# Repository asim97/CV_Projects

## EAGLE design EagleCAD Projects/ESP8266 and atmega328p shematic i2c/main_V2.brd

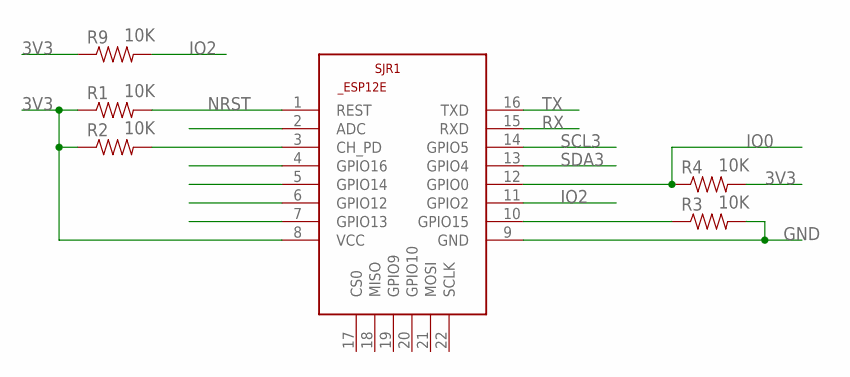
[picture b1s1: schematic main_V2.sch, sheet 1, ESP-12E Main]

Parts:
R1, R2, R3, R4, R9: 10K; 1206
SJR1: ESP8266-12EESP12E; ESP8266-ESP12E

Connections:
3V3: R1.1, R2.1, R4.2, R9.1, SJR1.8 (VCC); also elsewhere on the board
GND: R3.2, SJR1.9 (GND); also elsewhere on the board
IO0: R4.1, SJR1.12 (GPIO0); also elsewhere on the board
IO2: R9.2, SJR1.11 (GPIO2)
unnamed: R2.2, SJR1.3 (CH_PD)
unnamed: R3.1, SJR1.10 (GPIO15)
NRST: R1.2, SJR1.1 (REST); also elsewhere on the board
RX: SJR1.15 (RXD); also elsewhere on the board
SCL3: SJR1.14 (GPIO5); also elsewhere on the board
SDA3: SJR1.13 (GPIO4); also elsewhere on the board
TX: SJR1.16 (TXD); also elsewhere on the board

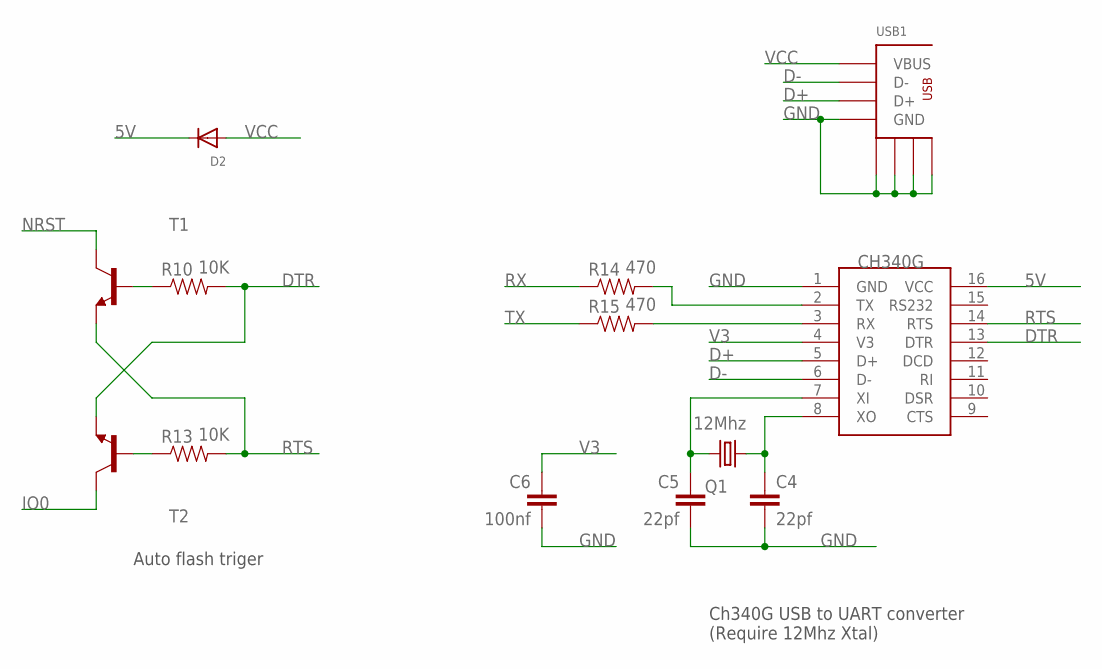
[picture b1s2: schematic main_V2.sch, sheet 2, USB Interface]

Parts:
C4, C5: 22pf; C1206K
C6: 100nf; C1206K
D2: DIODESMA; SMADIODE
Q1: 12Mhz; CSM-7X-DU
R10, R13: 10K; 1206
R14, R15: 470; 1206
T1, T2: MMBT5551LT1-NPN-SOT23-BEC; SOT23-BEC
U$1: CH340G; SOIC16
USB1: USB3MINI; USB-MB-S

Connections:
5V: D2.C, U$1.16 (VCC); also elsewhere on the board
D+: U$1.5 (D+), USB1.D+
D-: U$1.6 (D-), USB1.D-
DTR: R10.2, T2.E, U$1.13 (DTR)
GND: C4.2, C5.2, C6.2, U$1.1 (GND), USB1.GND, USB1.P$1 (GND), USB1.P$2 (GND), USB1.P$3 (GND), USB1.P$4 (GND); also elsewhere on the board
IO0: T2.C; also elsewhere on the board
unnamed: C4.1, Q1.1, U$1.8 (XO)
unnamed: C5.1, Q1.2, U$1.7 (XI)
unnamed: R10.1, T1.B
unnamed: R13.1, T2.B
unnamed: R15.2, U$1.3 (RX)
unnamed: R14.2, U$1.2 (TX)
NRST: T1.C; also elsewhere on the board
RTS: R13.2, T1.E, U$1.14 (RTS)
RX: R14.1; also elsewhere on the board
TX: R15.1; also elsewhere on the board
V3: C6.1, U$1.4 (V3)
VCC: D2.A, USB1.VBUS

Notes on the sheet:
Auto flash triger
Ch340G USB to UART converter (Require 12Mhz Xtal)

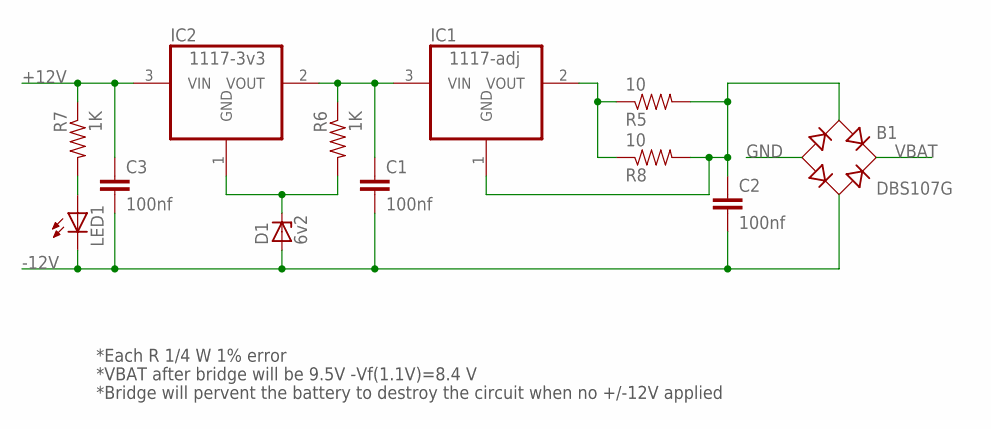
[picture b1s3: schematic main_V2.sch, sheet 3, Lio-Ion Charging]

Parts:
B1: DBS107G; DBS
C1, C2, C3: 100nf; C1206K
D1: 6v2; SOT23
IC1: 1117-adj; SOT223
IC2: 1117-3v3; SOT223
LED1: LEDSMT1206; 1206
R5, R8: 10; 1206
R6, R7: 1K; 1206

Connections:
+12V: C3.1, IC2.3 (VIN), R7.1
-12V: B1.AC2, C1.2, C2.2, C3.2, D1.1 (A), LED1.C
GND: B1.-; also elsewhere on the board
unnamed: D1.3 (C), IC2.1 (GND), R6.2
unnamed: B1.AC1, C2.1, IC1.1 (GND), R5.2, R8.2
unnamed: IC1.2 (VOUT), R5.1, R8.1
unnamed: C1.1, IC1.3 (VIN), IC2.2 (VOUT), R6.1
unnamed: LED1.A, R7.2
VBAT: B1.+; also elsewhere on the board

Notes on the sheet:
*Each R 1/4 W 1% error
*VBAT after bridge will be 9.5V -Vf(1.1V)=8.4 V
*Bridge will pervent the battery to destroy the circuit when no +/-12V applied

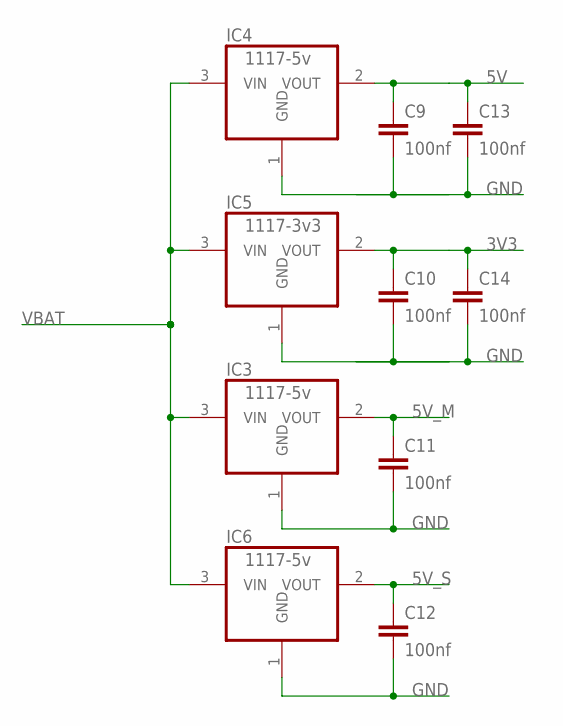
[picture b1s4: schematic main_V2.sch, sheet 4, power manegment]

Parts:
C9, C10, C11, C12, C13, C14: 100nf; C1206K
IC3, IC4, IC6: 1117-5v; SOT223
IC5: 1117-3v3; SOT223

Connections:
3V3: C10.1, C14.1, IC5.2 (VOUT); also elsewhere on the board
5V: C9.1, C13.1, IC4.2 (VOUT); also elsewhere on the board
5V_M: C11.1, IC3.2 (VOUT); also elsewhere on the board
5V_S: C12.1, IC6.2 (VOUT)
GND: C9.2, C10.2, C11.2, C12.2, C13.2, C14.2, IC3.1 (GND), IC4.1 (GND), IC5.1 (GND), IC6.1 (GND); also elsewhere on the board
VBAT: IC3.3 (VIN), IC4.3 (VIN), IC5.3 (VIN), IC6.3 (VIN); also elsewhere on the board

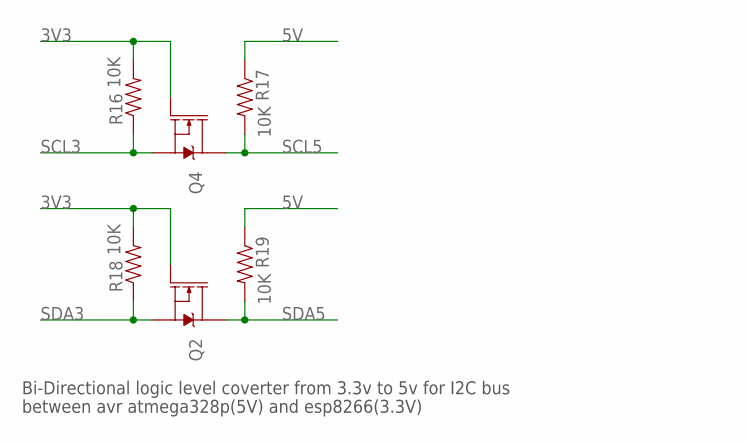
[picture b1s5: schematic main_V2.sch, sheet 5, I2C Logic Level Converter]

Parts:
Q2, Q4: MOSFET-NCH-BSS138; SOT23-3
R16, R17, R18, R19: 10K; 1206

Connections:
3V3: Q2.1 (G), Q4.1 (G), R16.2, R18.2; also elsewhere on the board
5V: R17.1, R19.1; also elsewhere on the board
SCL3: Q4.2 (S), R16.1; also elsewhere on the board
SCL5: Q4.3 (D), R17.2; also elsewhere on the board
SDA3: Q2.2 (S), R18.1; also elsewhere on the board
SDA5: Q2.3 (D), R19.2; also elsewhere on the board

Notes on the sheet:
Bi-Directional logic level coverter from 3.3v to 5v for I2C bus
between avr atmega328p(5V) and esp8266(3.3V)

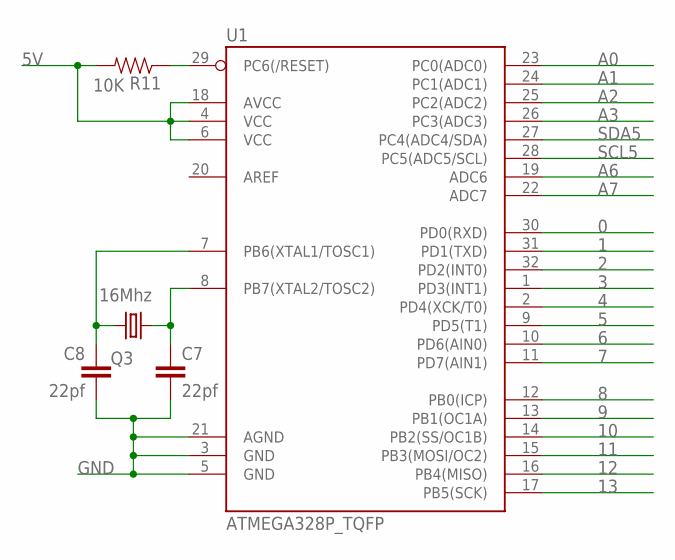
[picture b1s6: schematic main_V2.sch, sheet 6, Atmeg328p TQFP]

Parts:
C7, C8: 22pf; C1206K
Q3: 16Mhz; CSM-7X-DU
R11: 10K; 1206
U1: ATMEGA328P_TQFP; TQFP32-08

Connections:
0: U1.30 (PD0(RXD))
1: U1.31 (PD1(TXD))
2: U1.32 (PD2(INT0))
3: U1.1 (PD3(INT1))
4: U1.2 (PD4(XCK/T0))
5: U1.9 (PD5(T1))
5V: R11.2, U1.4 (VCC), U1.6 (VCC), U1.18 (AVCC); also elsewhere on the board
6: U1.10 (PD6(AIN0))
7: U1.11 (PD7(AIN1))
8: U1.12 (PB0(ICP))
9: U1.13 (PB1(OC1A))
10: U1.14 (PB2(SS/OC1B))
11: U1.15 (PB3(MOSI/OC2))
12: U1.16 (PB4(MISO))
13: U1.17 (PB5(SCK))
A0: U1.23 (PC0(ADC0))
A1: U1.24 (PC1(ADC1))
A2: U1.25 (PC2(ADC2))
A3: U1.26 (PC3(ADC3))
A6: U1.19 (ADC6)
A7: U1.22 (ADC7)
GND: C7.2, C8.2, U1.3 (GND), U1.5 (GND), U1.21 (AGND); also elsewhere on the board
unnamed: C7.1, Q3.1, U1.8 (PB7(XTAL2/TOSC2))
unnamed: C8.1, Q3.2, U1.7 (PB6(XTAL1/TOSC1))
unnamed: R11.1, U1.29 (PC6(/RESET))
SCL5: U1.28 (PC5(ADC5/SCL)); also elsewhere on the board
SDA5: U1.27 (PC4(ADC4/SDA)); also elsewhere on the board

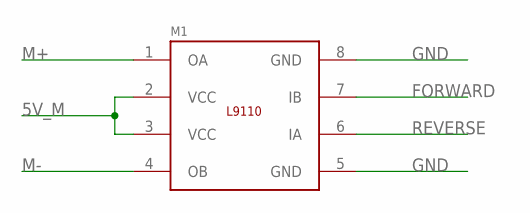
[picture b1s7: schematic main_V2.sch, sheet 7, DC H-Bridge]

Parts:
M1: L9110; SO8P

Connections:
5V_M: M1.2 (VCC), M1.3 (VCC); also elsewhere on the board
FORWARD: M1.7 (IB)
GND: M1.5 (GND), M1.8 (GND); also elsewhere on the board
M+: M1.1 (OA)
M-: M1.4 (OB)
REVERSE: M1.6 (IA)

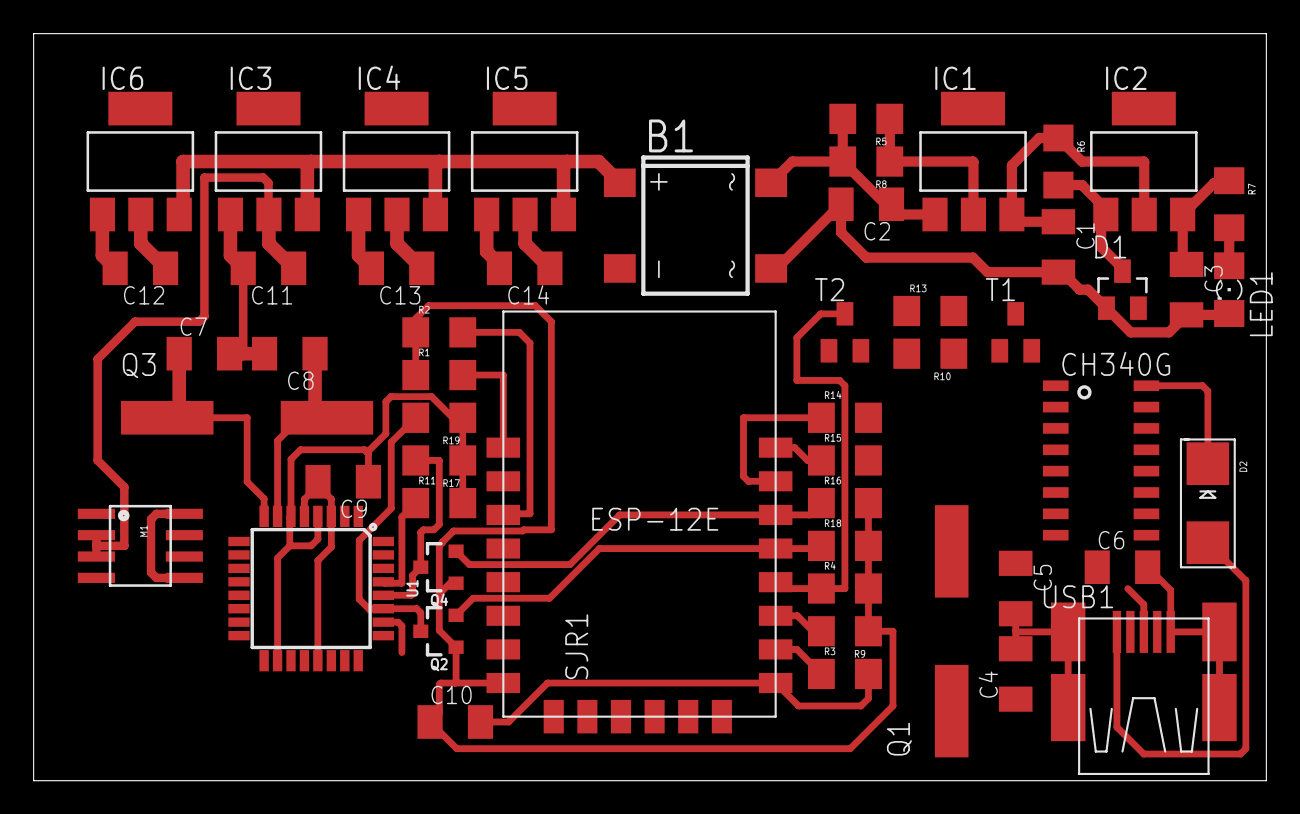
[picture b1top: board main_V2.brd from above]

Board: 2 copper layers, 73.3 x 44.4 mm, 53 parts (0 on the bottom side), 39 nets.

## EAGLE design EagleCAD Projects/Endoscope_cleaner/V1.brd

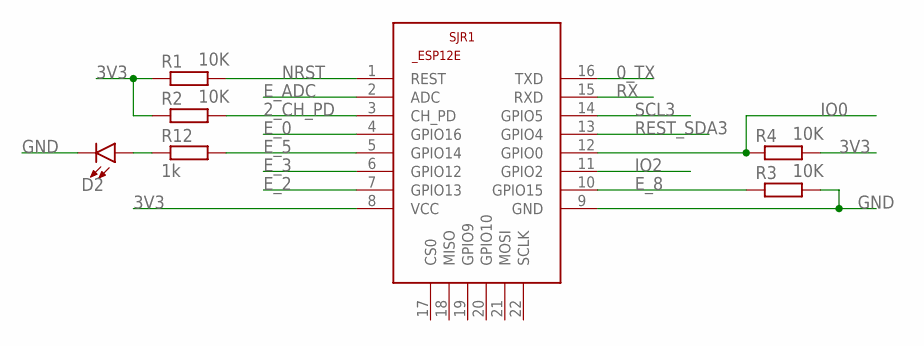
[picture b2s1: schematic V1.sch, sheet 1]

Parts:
D2: LED5MM; LED_5MM
R1, R2, R3, R4: 10K; 0207/10
R12: 1k; 0207/10
SJR1: ESP8266-12EESP12E; ESP8266-ESP12E

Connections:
0_TX: SJR1.16 (TXD); also elsewhere on the board
2_CH_PD: R2.2, SJR1.3 (CH_PD); also elsewhere on the board
3V3: R1.1, R2.1, R4.2, SJR1.8 (VCC); also elsewhere on the board
E_0: SJR1.4 (GPIO16)
E_2: SJR1.7 (GPIO13)
E_3: SJR1.6 (GPIO12)
E_5: R12.2, SJR1.5 (GPIO14)
E_8: R3.1, SJR1.10 (GPIO15)
E_ADC: SJR1.2 (ADC)
GND: D2.K (C), R3.2, SJR1.9 (GND); also elsewhere on the board
IO0: R4.1, SJR1.12 (GPIO0)
IO2: SJR1.11 (GPIO2)
unnamed: D2.A, R12.1
NRST: R1.2, SJR1.1 (REST)
REST_SDA3: SJR1.13 (GPIO4); also elsewhere on the board
RX: SJR1.15 (RXD); also elsewhere on the board
SCL3: SJR1.14 (GPIO5)

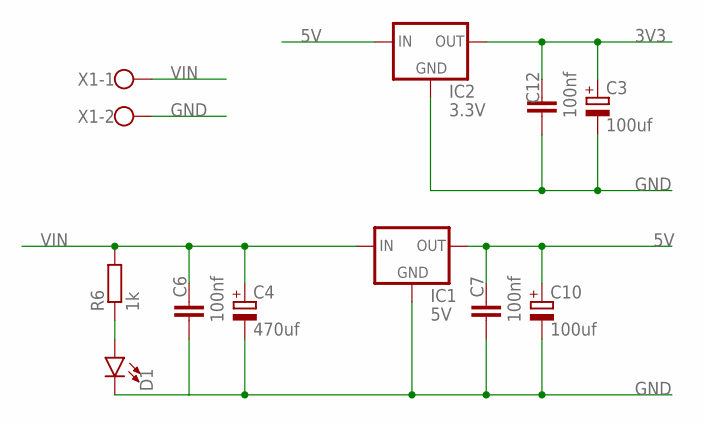
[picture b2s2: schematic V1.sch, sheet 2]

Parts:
C3, C10: 100uf; E3,5-8
C4: 470uf; E3,5-8
C6, C7, C12: 100nf; C050-030X075
D1: LED5MM; LED_5MM
IC1: 5V; 78XXL
IC2: 3.3V; 78XXL
R6: 1k; 0207/10
X1: W237-102

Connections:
3V3: C3.+, C12.2, IC2.OUT; also elsewhere on the board
5V: C7.2, C10.+, IC1.OUT, IC2.IN; also elsewhere on the board
GND: C3.-, C4.-, C6.1, C7.1, C10.-, C12.1, D1.K (C), IC1.GND, IC2.GND, X1.2; also elsewhere on the board
unnamed: D1.A, R6.1
VIN: C4.+, C6.2, IC1.IN, R6.2, X1.1

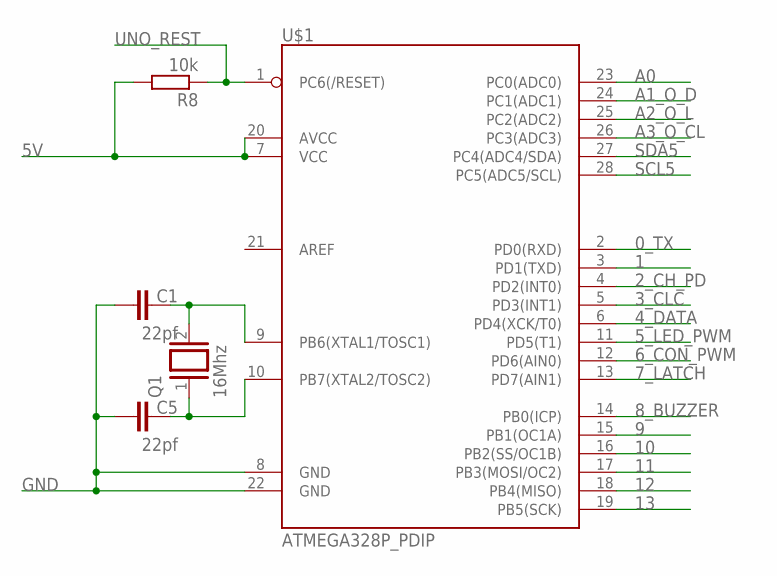
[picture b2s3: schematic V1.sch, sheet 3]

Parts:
C1, C5: 22pf; C050-030X075
Q1: 16Mhz; QS
R8: 10k; 0207/10
U$1: ATMEGA328P_PDIP; DIL-28-3

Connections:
0_TX: U$1.2 (PD0(RXD)); also elsewhere on the board
1: U$1.3 (PD1(TXD)); also elsewhere on the board
2_CH_PD: U$1.4 (PD2(INT0)); also elsewhere on the board
3_CLC: U$1.5 (PD3(INT1)); also elsewhere on the board
4_DATA: U$1.6 (PD4(XCK/T0)); also elsewhere on the board
5V: R8.2, U$1.7 (VCC), U$1.20 (AVCC); also elsewhere on the board
5_LED_PWM: U$1.11 (PD5(T1)); also elsewhere on the board
6_CON_PWM: U$1.12 (PD6(AIN0)); also elsewhere on the board
7_LATCH: U$1.13 (PD7(AIN1)); also elsewhere on the board
8_BUZZER: U$1.14 (PB0(ICP)); also elsewhere on the board
9: U$1.15 (PB1(OC1A)); also elsewhere on the board
10: U$1.16 (PB2(SS/OC1B)); also elsewhere on the board
11: U$1.17 (PB3(MOSI/OC2)); also elsewhere on the board
12: U$1.18 (PB4(MISO))
13: U$1.19 (PB5(SCK))
A0: U$1.23 (PC0(ADC0))
A1_O_D: U$1.24 (PC1(ADC1)); also elsewhere on the board
A2_O_L: U$1.25 (PC2(ADC2)); also elsewhere on the board
A3_O_CL: U$1.26 (PC3(ADC3)); also elsewhere on the board
GND: C1.1, C5.1, U$1.8 (GND), U$1.22 (GND); also elsewhere on the board
unnamed: C5.2, Q1.1, U$1.10 (PB7(XTAL2/TOSC2))
unnamed: C1.2, Q1.2, U$1.9 (PB6(XTAL1/TOSC1))
SCL5: U$1.28 (PC5(ADC5/SCL))
SDA5: U$1.27 (PC4(ADC4/SDA))
UNO_REST: R8.1, U$1.1 (PC6(/RESET)); also elsewhere on the board

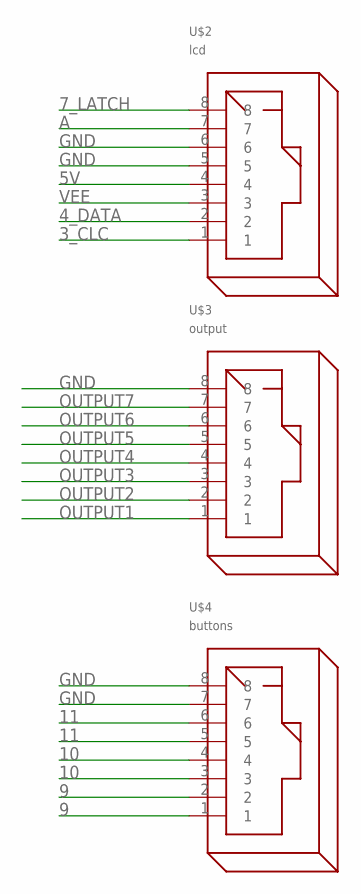
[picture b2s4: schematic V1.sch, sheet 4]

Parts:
U$2: lcd; RJ45
U$3: output; RJ45
U$4: buttons; RJ45

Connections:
3_CLC: U$2.1; also elsewhere on the board
4_DATA: U$2.2; also elsewhere on the board
5V: U$2.4; also elsewhere on the board
7_LATCH: U$2.8; also elsewhere on the board
9: U$4.1, U$4.2; also elsewhere on the board
10: U$4.3, U$4.4; also elsewhere on the board
11: U$4.5, U$4.6; also elsewhere on the board
A: U$2.7; also elsewhere on the board
GND: U$2.5, U$2.6, U$3.8, U$4.7, U$4.8; also elsewhere on the board
OUTPUT1: U$3.1; also elsewhere on the board
OUTPUT2: U$3.2; also elsewhere on the board
OUTPUT3: U$3.3; also elsewhere on the board
OUTPUT4: U$3.4; also elsewhere on the board
OUTPUT5: U$3.5; also elsewhere on the board
OUTPUT6: U$3.6; also elsewhere on the board
OUTPUT7: U$3.7; also elsewhere on the board
VEE: U$2.3; also elsewhere on the board

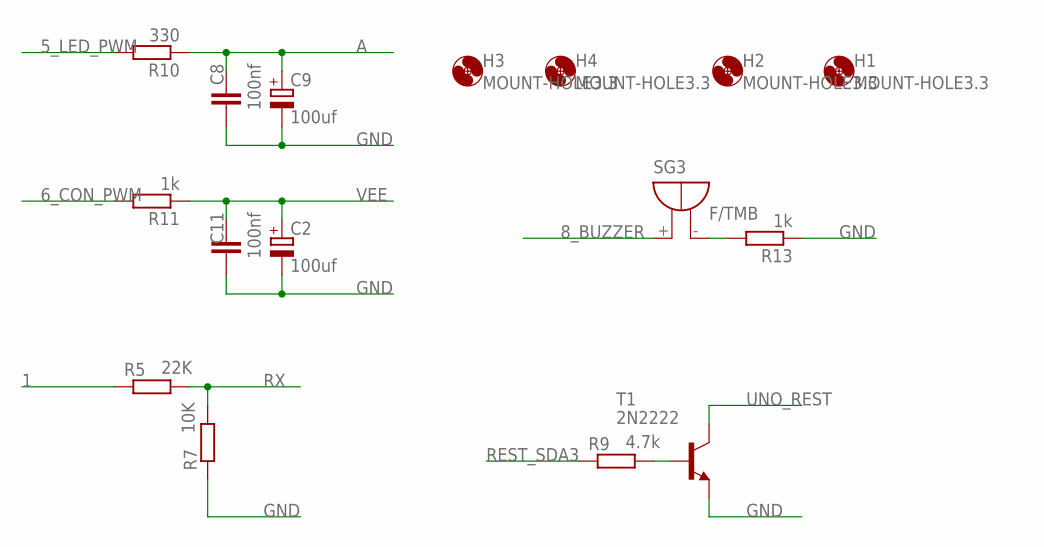
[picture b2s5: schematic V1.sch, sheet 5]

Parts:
C2, C9: 100uf; E3,5-8
C8, C11: 100nf; C050-030X075
H1, H2, H3, H4: MOUNT-HOLE3.3; 3,3
R5: 22K; 0207/10
R7: 10K; 0207/10
R9: 4.7k; 0207/10
R10: 330; 0207/10
R11, R13: 1k; 0207/10
SG3: F/TMB
T1: 2N2222; TO92-EBC-OVAL

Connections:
1: R5.1; also elsewhere on the board
5_LED_PWM: R10.2; also elsewhere on the board
6_CON_PWM: R11.2; also elsewhere on the board
8_BUZZER: SG3.+; also elsewhere on the board
A: C8.2, C9.+, R10.1; also elsewhere on the board
GND: C2.-, C8.1, C9.-, C11.1, R7.1, R13.1, T1.E; also elsewhere on the board
unnamed: R9.2, T1.B
unnamed: R13.2, SG3.-
REST_SDA3: R9.1; also elsewhere on the board
RX: R5.2, R7.2; also elsewhere on the board
UNO_REST: T1.C; also elsewhere on the board
VEE: C2.+, C11.2, R11.1; also elsewhere on the board

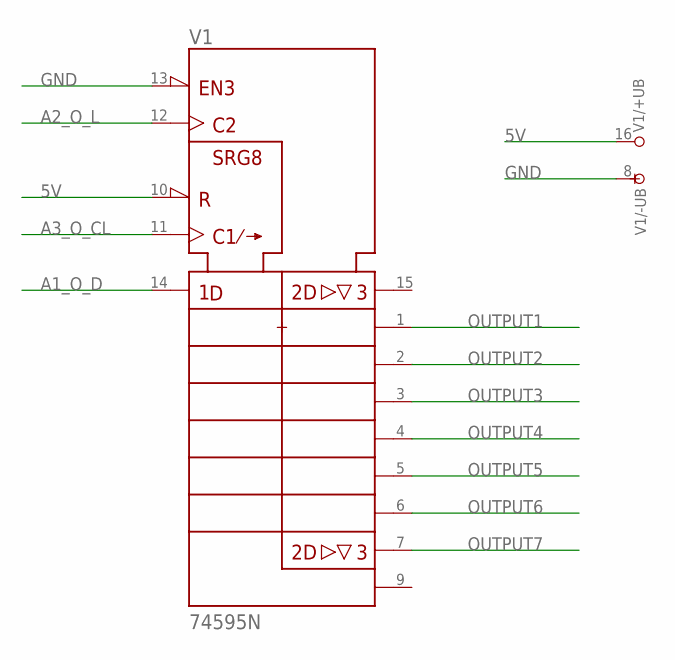
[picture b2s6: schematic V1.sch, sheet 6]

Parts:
V1: 74595N; DIL16

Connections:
5V: V1.10 (!SRCLR), V1.16 (+UB); also elsewhere on the board
A1_O_D: V1.14 (SER); also elsewhere on the board
A2_O_L: V1.12 (RCK); also elsewhere on the board
A3_O_CL: V1.11 (SRCK); also elsewhere on the board
GND: V1.8 (-UB), V1.13 (!G); also elsewhere on the board
OUTPUT1: V1.1 (QB); also elsewhere on the board
OUTPUT2: V1.2 (QC); also elsewhere on the board
OUTPUT3: V1.3 (QD); also elsewhere on the board
OUTPUT4: V1.4 (QE); also elsewhere on the board
OUTPUT5: V1.5 (QF); also elsewhere on the board
OUTPUT6: V1.6 (QG); also elsewhere on the board
OUTPUT7: V1.7 (QH); also elsewhere on the board

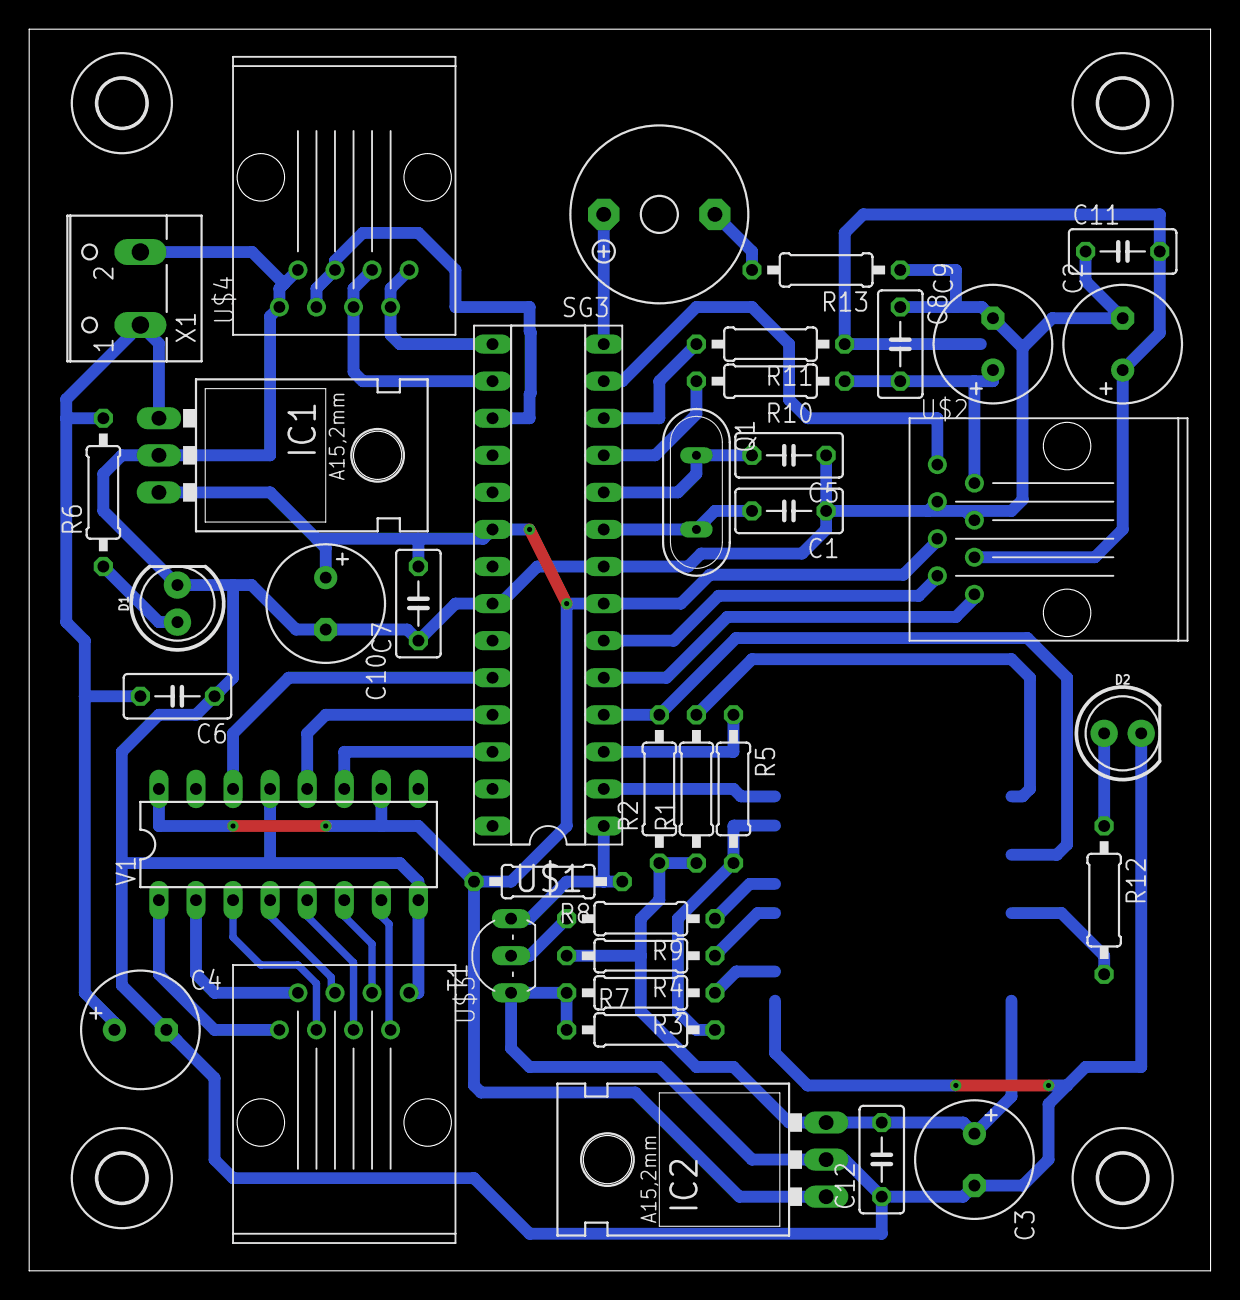
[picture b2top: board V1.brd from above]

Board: 2 copper layers, 81.0 x 85.1 mm, 43 parts (1 on the bottom side), 41 nets.

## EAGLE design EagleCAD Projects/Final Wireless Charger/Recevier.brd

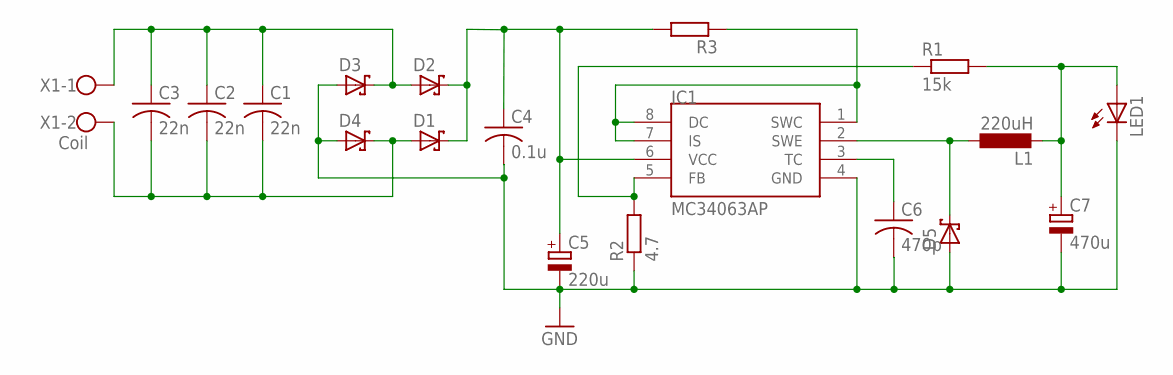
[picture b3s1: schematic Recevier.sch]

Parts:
C1, C2, C3: 22n; C050-025X075
C4: 0.1u; C050-025X075
C5: 220u; E5-10,5
C6: 470p; C050-025X075
C7: 470u; E3,5-8
D1, D2, D3, D4, D5: 1N5819-B; DO41-7.6
IC1: MC34063AP; DIL08
L1: 220uH; 2200-12.7
LED1: LED3MM
R1: 15k; 0207/10
R2: 4.7; 0207/10
R3: R-EU_0207/10; 0207/10
X1: Coil; W237-102

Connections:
GND: C4.2, C5.-, C6.2, C7.-, D3.A, D4.A, D5.A, IC1.4 (GND), LED1.K (C), R2.1
unnamed: IC1.1 (SWC), IC1.7 (IS), IC1.8 (DC), R3.1
unnamed: C4.1, C5.+, D1.C, D2.C, IC1.6 (VCC), R3.2
unnamed: IC1.5 (FB), R1.1, R2.2
unnamed: C6.1, IC1.3 (TC)
unnamed: C1.1, C2.1, C3.1, D2.A, D3.C, X1.1
unnamed: D5.C, IC1.2 (SWE), L1.1
unnamed: C1.2, C2.2, C3.2, D1.A, D4.C, X1.2
unnamed: C7.+, L1.2, LED1.A, R1.2

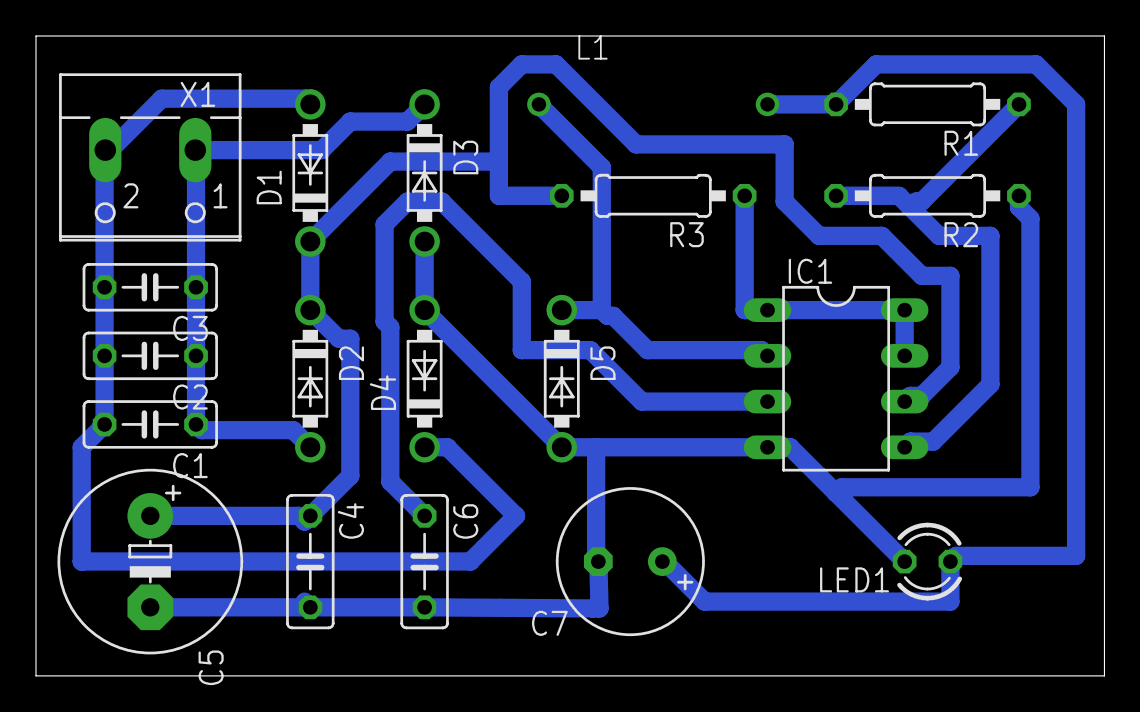
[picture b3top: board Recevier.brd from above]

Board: 2 copper layers, 59.4 x 35.5 mm, 19 parts (0 on the bottom side), 9 nets.

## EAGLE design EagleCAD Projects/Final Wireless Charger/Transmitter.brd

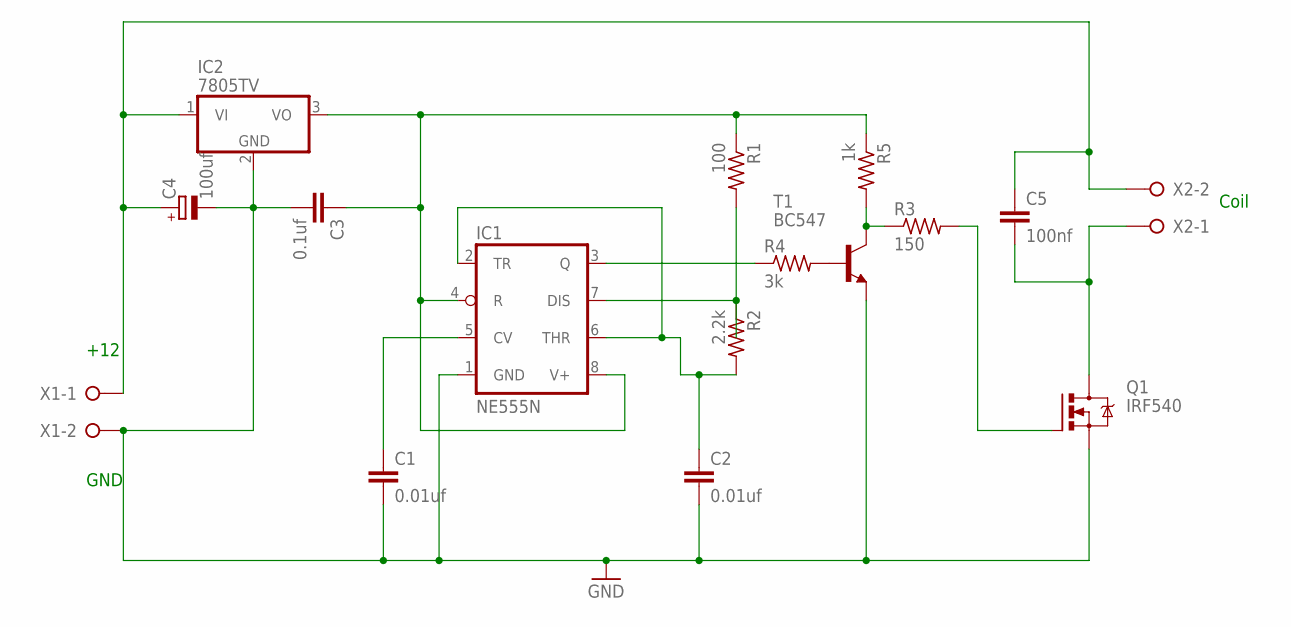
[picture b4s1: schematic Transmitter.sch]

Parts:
C1, C2: 0.01uf; C025-030X050
C3: 0.1uf; C025-030X050
C4: 100uf; E2,5-6E
C5: 100nf; C102-064X133
IC1: NE555N; DIL08
IC2: 7805TV; TO220V
Q1: IRF540; TO220BV
R1: 100; 0207/10
R2: 2.2k; 0207/10
R3: 150; 0207/10
R4: 3k; 0207/10
R5: 1k; 0207/10
T1: BC547; TO92
X1, X2: W237-02P; W237-132

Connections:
GND: C1.2, C2.2, C3.2, C4.-, IC1.1 (GND), IC2.2 (GND), Q1.S, T1.1 (E), X1.2
unnamed: C4.+, C5.1, IC2.1 (VI), X1.1, X2.2
unnamed: C3.1, IC1.4 (R), IC1.8 (V+), IC2.3 (VO), R1.1, R5.1
unnamed: R4.2, T1.2 (B)
unnamed: IC1.7 (DIS), R1.2, R2.1
unnamed: C2.1, IC1.2 (TR), IC1.6 (THR), R2.2
unnamed: R3.1, R5.2, T1.3 (C)
unnamed: C1.1, IC1.5 (CV)
unnamed: IC1.3 (Q), R4.1
unnamed: Q1.G, R3.2
unnamed: C5.2, Q1.D, X2.1

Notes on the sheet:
+12
GND
Coil

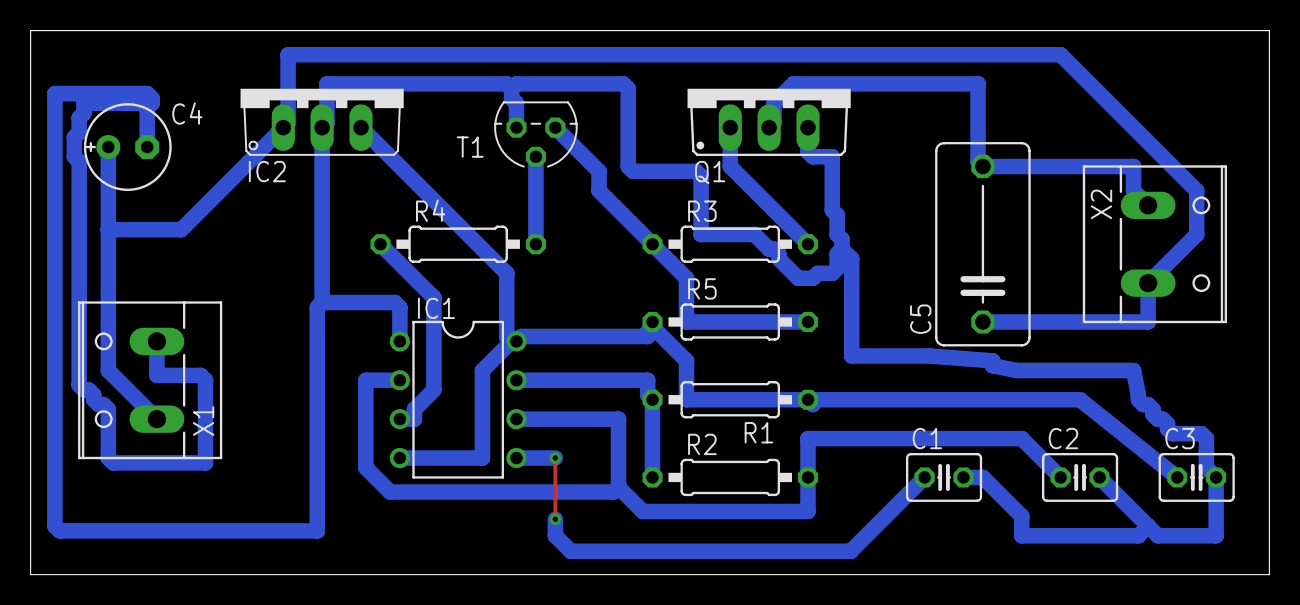
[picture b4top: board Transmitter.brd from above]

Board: 2 copper layers, 81.0 x 35.6 mm, 16 parts (0 on the bottom side), 11 nets.

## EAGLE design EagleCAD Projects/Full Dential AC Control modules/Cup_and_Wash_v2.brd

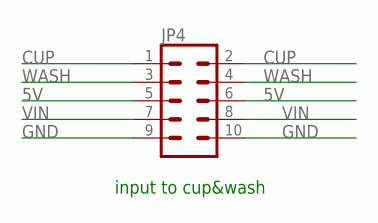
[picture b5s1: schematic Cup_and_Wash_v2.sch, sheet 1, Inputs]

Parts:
JP4: CONN_05X2PTH; 2X5

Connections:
5V: JP4.5, JP4.6; also elsewhere on the board
CUP: JP4.1, JP4.2; also elsewhere on the board
GND: JP4.9, JP4.10; also elsewhere on the board
VIN: JP4.7, JP4.8; also elsewhere on the board
WASH: JP4.3, JP4.4; also elsewhere on the board

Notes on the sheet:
input to cup&wash

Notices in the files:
parts and their libraries:
SparkFun-LED: Licensing: Creative Commons ShareAlike 4.0 International - https://creativecommons.org/licenses/by-sa/4.0
vreg-pulse: 2009 Draw by Ivan A-R. License CC-BY-SA 3.0
